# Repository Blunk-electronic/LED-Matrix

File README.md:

# LED-Matrix
A demo project to demonstrate a 2-layer PCB design

some images:

watch a short movie <http://www.blunk-electronic.de/download/dr-simon.mp4>

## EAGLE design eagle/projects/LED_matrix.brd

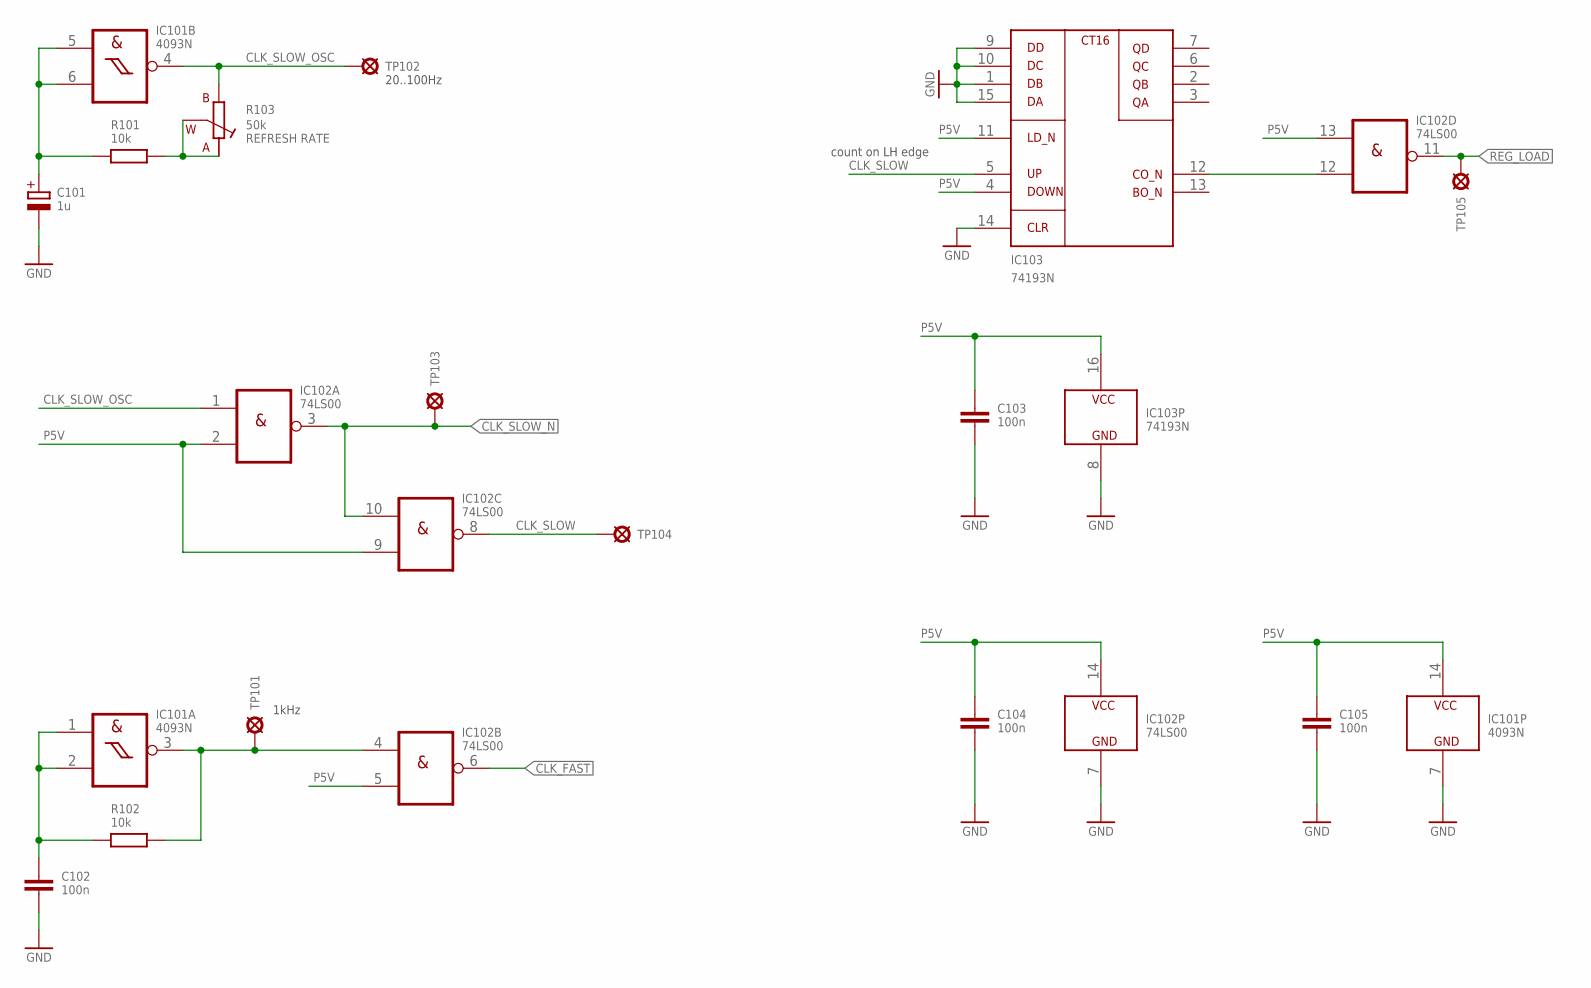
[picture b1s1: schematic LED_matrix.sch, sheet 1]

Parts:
C101: 1u; T_RADIAL_5MM_GRID_2.54MM; PART_CODE_BEL C_PAC_T_RADIAL_5mm_PITCH_2mm54_VAL_1u
C102, C103, C104, C105: 100n; T_DISC_4MM_PITCH_5MM; PART_CODE_BEL C_PAC_T_DISC_7mm_PITCH_5mm_VAL_100n
IC101: 4093N; T_NDIP14
IC102: 74LS00; T_NDIP14; PART_CODE_BEL IC_PAC_T_NDIP14_VAL_SN74LS00N
IC103: 74193N; T_NDIP16; PART_CODE_BEL IC_PAC_NDIP16_VAL_SN74193N
R101, R102: 10k; T_0207_PITCH_10MM; PART_CODE_BEL R_PAC_T_0207_PITCH_10mm_VAL_10k
R103: 50k; T_TRIM_PIHER_PT10_HORIZONTAL; PART_CODE_BEL R_PAC_T_TRIM_PIHER_PT10_HORIZONTAL_VAL_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
TP101, TP102, TP103, TP104, TP105: TEST_POINT_T_SMALL; T_TEST_POINT_SMALL

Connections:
CLK_FAST: IC102.6 (O); also elsewhere on the board
CLK_FAST_OSC: IC101.3 (O), IC102.4 (I0), R102.2, TP101.1
CLK_FAST_RC: C102.1, IC101.1 (I0), IC101.2 (I1), R102.1
CLK_SLOW: IC102.8 (O), IC103.5 (UP), TP104.1
CLK_SLOW_N: IC102.3 (O), IC102.10 (I0), TP103.1; also elsewhere on the board
CLK_SLOW_OSC: IC101.4 (O), IC102.1 (I0), R103.B, TP102.1
CLK_SLOW_RA: R101.2, R103.A, R103.W
CLK_SLOW_RC: C101.+, IC101.5 (I0), IC101.6 (I1), R101.1
CT_CO_N: IC102.12 (I1), IC103.12 (CO_N)
GND: C101.-, C102.2, C103.2, C104.2, C105.2, IC101.7 (GND), IC102.7 (GND), IC103.1 (DB), IC103.8 (GND), IC103.9 (DD), IC103.10 (DC), IC103.14 (CLR), IC103.15 (DA); also elsewhere on the board
P5V: C103.1, C104.1, C105.1, IC101.14 (VCC), IC102.2 (I1), IC102.5 (I1), IC102.9 (I1), IC102.13 (I0), IC102.14 (VCC), IC103.4 (DOWN), IC103.11 (LD_N), IC103.16 (VCC); also elsewhere on the board
REG_LOAD: IC102.11 (O), TP105.1; also elsewhere on the board

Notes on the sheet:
count on LH edge
20..100Hz
1kHz

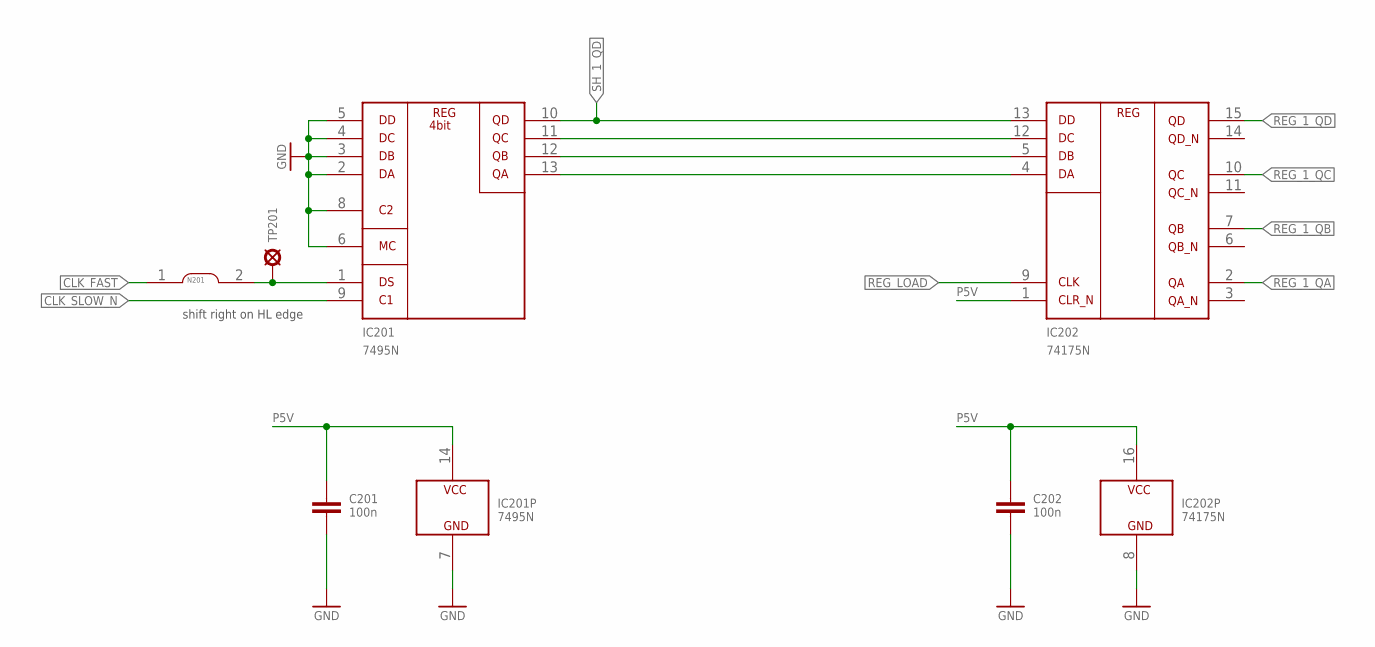
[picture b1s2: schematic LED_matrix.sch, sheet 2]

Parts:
C201, C202: 100n; T_DISC_4MM_PITCH_5MM; PART_CODE_BEL C_PAC_T_DISC_7mm_PITCH_5mm_VAL_100n
IC201: 7495N; T_NDIP14; PART_CODE_BEL IC_PAC_T_NDIP14_VAL_SN7495N
IC202: 74175N; T_NDIP16; PART_CODE_BEL IC_PAC_NDIP16_VAL_SN74175N
N201: NET_CHANGER-S-0.3MM; S_NET_CHANGER_0.3MM
TP201: TEST_POINT_T_SMALL; T_TEST_POINT_SMALL

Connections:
CLK_FAST: N201.1; also elsewhere on the board
CLK_SLOW_N: IC201.9 (C1); also elsewhere on the board
GND: C201.2, C202.2, IC201.2 (DA), IC201.3 (DB), IC201.4 (DC), IC201.5 (DD), IC201.6 (MC), IC201.7 (GND), IC201.8 (C2), IC202.8 (GND); also elsewhere on the board
P5V: C201.1, C202.1, IC201.14 (VCC), IC202.1 (CLR_N), IC202.16 (VCC); also elsewhere on the board
REG_1_QA: IC202.2 (QA); also elsewhere on the board
REG_1_QB: IC202.7 (QB); also elsewhere on the board
REG_1_QC: IC202.10 (QC); also elsewhere on the board
REG_1_QD: IC202.15 (QD); also elsewhere on the board
REG_LOAD: IC202.9 (CLK); also elsewhere on the board
SH_1_DS: IC201.1 (DS), N201.2, TP201.1
SH_1_QA: IC201.13 (QA), IC202.4 (DA)
SH_1_QB: IC201.12 (QB), IC202.5 (DB)
SH_1_QC: IC201.11 (QC), IC202.12 (DC)
SH_1_QD: IC201.10 (QD), IC202.13 (DD); also elsewhere on the board

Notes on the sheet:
shift right on HL edge

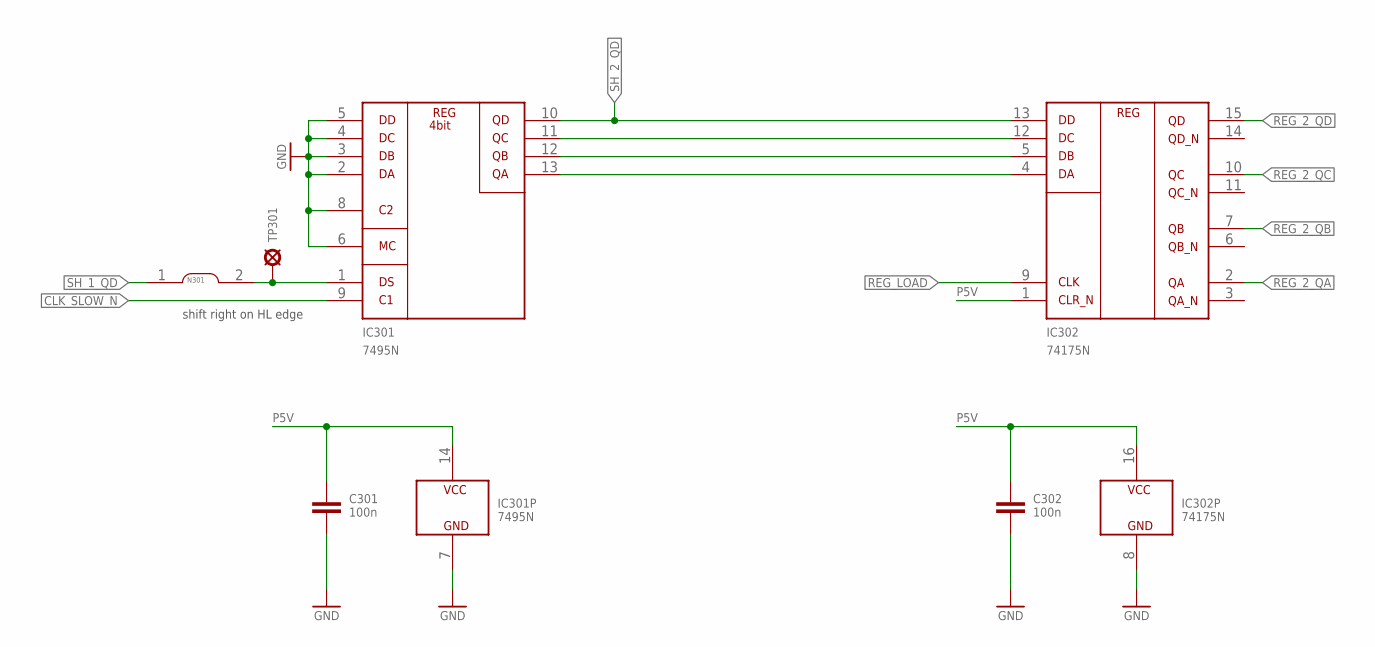
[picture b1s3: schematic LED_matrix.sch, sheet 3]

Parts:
C301, C302: 100n; T_DISC_4MM_PITCH_5MM; PART_CODE_BEL C_PAC_T_DISC_7mm_PITCH_5mm_VAL_100n
IC301: 7495N; T_NDIP14; PART_CODE_BEL IC_PAC_T_NDIP14_VAL_SN7495N
IC302: 74175N; T_NDIP16; PART_CODE_BEL IC_PAC_NDIP16_VAL_SN74175N
N301: NET_CHANGER-S-0.3MM; S_NET_CHANGER_0.3MM
TP301: TEST_POINT_T_SMALL; T_TEST_POINT_SMALL

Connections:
CLK_SLOW_N: IC301.9 (C1); also elsewhere on the board
GND: C301.2, C302.2, IC301.2 (DA), IC301.3 (DB), IC301.4 (DC), IC301.5 (DD), IC301.6 (MC), IC301.7 (GND), IC301.8 (C2), IC302.8 (GND); also elsewhere on the board
P5V: C301.1, C302.1, IC301.14 (VCC), IC302.1 (CLR_N), IC302.16 (VCC); also elsewhere on the board
REG_2_QA: IC302.2 (QA); also elsewhere on the board
REG_2_QB: IC302.7 (QB); also elsewhere on the board
REG_2_QC: IC302.10 (QC); also elsewhere on the board
REG_2_QD: IC302.15 (QD); also elsewhere on the board
REG_LOAD: IC302.9 (CLK); also elsewhere on the board
SH_1_DS1: IC301.1 (DS), N301.2, TP301.1
SH_1_QD: N301.1; also elsewhere on the board
SH_2_QA: IC301.13 (QA), IC302.4 (DA)
SH_2_QB: IC301.12 (QB), IC302.5 (DB)
SH_2_QC: IC301.11 (QC), IC302.12 (DC)
SH_2_QD: IC301.10 (QD), IC302.13 (DD); also elsewhere on the board

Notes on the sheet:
shift right on HL edge

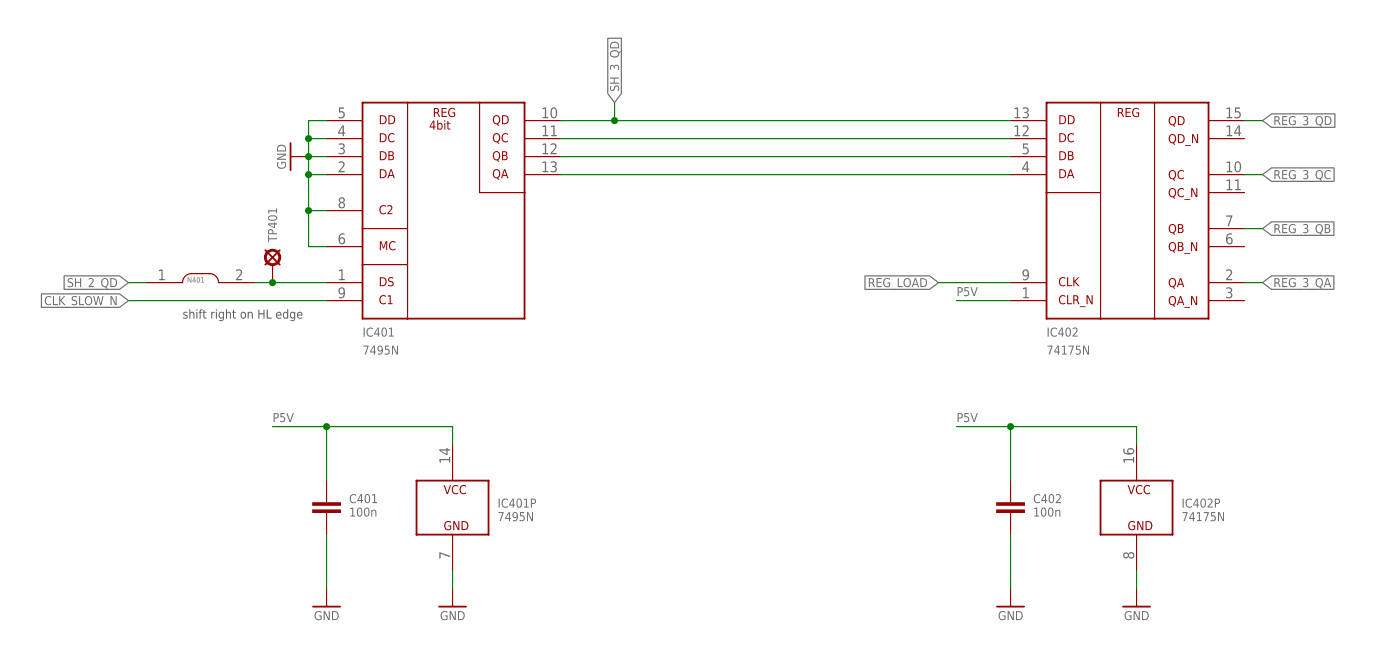
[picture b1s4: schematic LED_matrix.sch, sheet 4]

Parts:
C401, C402: 100n; T_DISC_4MM_PITCH_5MM; PART_CODE_BEL C_PAC_T_DISC_7mm_PITCH_5mm_VAL_100n
IC401: 7495N; T_NDIP14; PART_CODE_BEL IC_PAC_T_NDIP14_VAL_SN7495N
IC402: 74175N; T_NDIP16; PART_CODE_BEL IC_PAC_NDIP16_VAL_SN74175N
N401: NET_CHANGER-S-0.3MM; S_NET_CHANGER_0.3MM
TP401: TEST_POINT_T_SMALL; T_TEST_POINT_SMALL

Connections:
CLK_SLOW_N: IC401.9 (C1); also elsewhere on the board
GND: C401.2, C402.2, IC401.2 (DA), IC401.3 (DB), IC401.4 (DC), IC401.5 (DD), IC401.6 (MC), IC401.7 (GND), IC401.8 (C2), IC402.8 (GND); also elsewhere on the board
P5V: C401.1, C402.1, IC401.14 (VCC), IC402.1 (CLR_N), IC402.16 (VCC); also elsewhere on the board
REG_3_QA: IC402.2 (QA); also elsewhere on the board
REG_3_QB: IC402.7 (QB); also elsewhere on the board
REG_3_QC: IC402.10 (QC); also elsewhere on the board
REG_3_QD: IC402.15 (QD); also elsewhere on the board
REG_LOAD: IC402.9 (CLK); also elsewhere on the board
SH_1_DS2: IC401.1 (DS), N401.2, TP401.1
SH_2_QD: N401.1; also elsewhere on the board
SH_3_QA: IC401.13 (QA), IC402.4 (DA)
SH_3_QB: IC401.12 (QB), IC402.5 (DB)
SH_3_QC: IC401.11 (QC), IC402.12 (DC)
SH_3_QD: IC401.10 (QD), IC402.13 (DD); also elsewhere on the board

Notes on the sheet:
shift right on HL edge

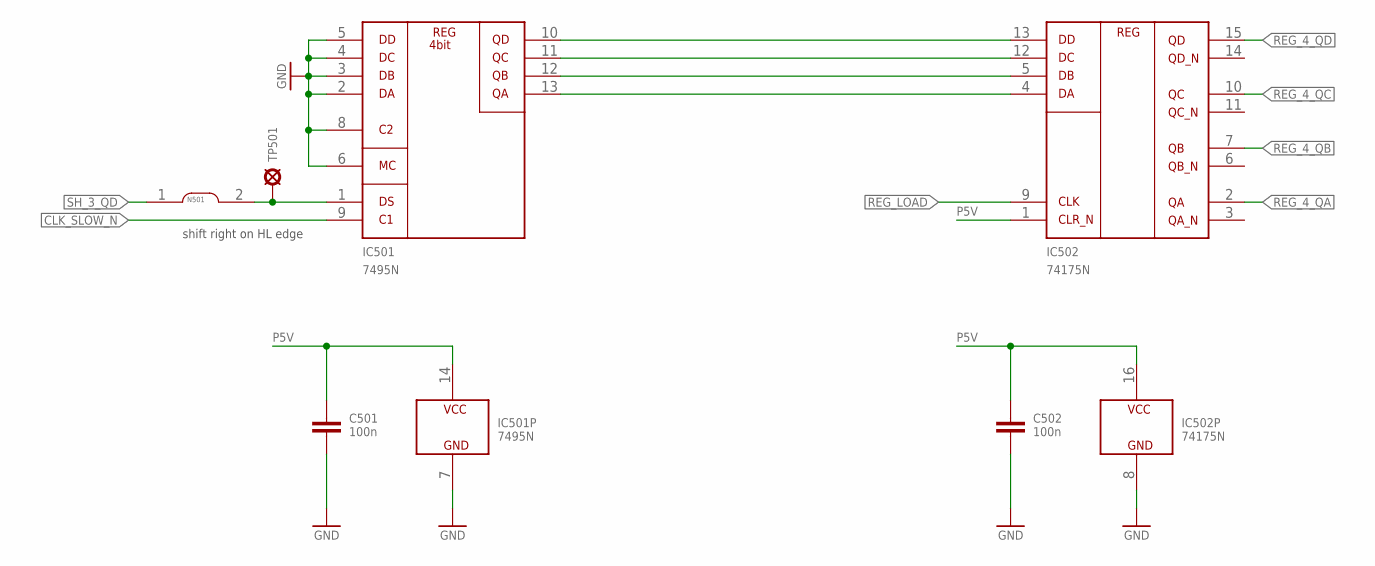
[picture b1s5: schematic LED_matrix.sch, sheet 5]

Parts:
C501, C502: 100n; T_DISC_4MM_PITCH_5MM; PART_CODE_BEL C_PAC_T_DISC_7mm_PITCH_5mm_VAL_100n
IC501: 7495N; T_NDIP14; PART_CODE_BEL IC_PAC_T_NDIP14_VAL_SN7495N
IC502: 74175N; T_NDIP16; PART_CODE_BEL IC_PAC_NDIP16_VAL_SN74175N
N501: NET_CHANGER-S-0.3MM; S_NET_CHANGER_0.3MM
TP501: TEST_POINT_T_SMALL; T_TEST_POINT_SMALL

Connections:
CLK_SLOW_N: IC501.9 (C1); also elsewhere on the board
GND: C501.2, C502.2, IC501.2 (DA), IC501.3 (DB), IC501.4 (DC), IC501.5 (DD), IC501.6 (MC), IC501.7 (GND), IC501.8 (C2), IC502.8 (GND); also elsewhere on the board
P5V: C501.1, C502.1, IC501.14 (VCC), IC502.1 (CLR_N), IC502.16 (VCC); also elsewhere on the board
REG_4_QA: IC502.2 (QA); also elsewhere on the board
REG_4_QB: IC502.7 (QB); also elsewhere on the board
REG_4_QC: IC502.10 (QC); also elsewhere on the board
REG_4_QD: IC502.15 (QD); also elsewhere on the board
REG_LOAD: IC502.9 (CLK); also elsewhere on the board
SH_1_DS3: IC501.1 (DS), N501.2, TP501.1
SH_3_QD: N501.1; also elsewhere on the board
SH_4_QA: IC501.13 (QA), IC502.4 (DA)
SH_4_QB: IC501.12 (QB), IC502.5 (DB)
SH_4_QC: IC501.11 (QC), IC502.12 (DC)
SH_4_QD: IC501.10 (QD), IC502.13 (DD)

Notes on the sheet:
shift right on HL edge

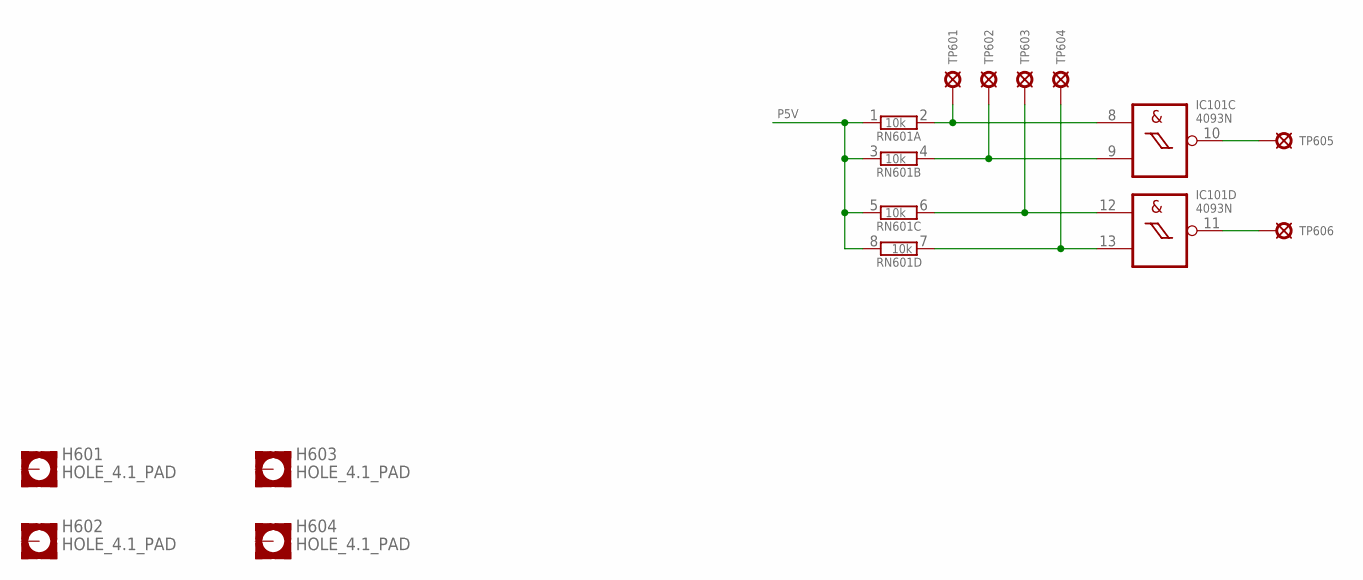
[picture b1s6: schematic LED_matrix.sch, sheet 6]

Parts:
H601, H602, H603, H604: HOLE_4.1_PAD; 4.1_PAD
IC101: 4093N; T_NDIP14
RN601: 10k; T_SIL8; PART_CODE_BEL RN_PAC_T_SIL8_VAL_10k
TP601, TP602, TP603, TP604, TP605, TP606: TEST_POINT_T_SMALL; T_TEST_POINT_SMALL

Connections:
P5V: RN601.1, RN601.3 (1), RN601.5 (1), RN601.8 (2); also elsewhere on the board
RSV_IN_1: IC101.8 (I0), RN601.2, TP601.1
RSV_IN_2: IC101.9 (I1), RN601.4 (2), TP602.1
RSV_IN_3: IC101.12 (I0), RN601.6 (2), TP603.1
RSV_IN_4: IC101.13 (I1), RN601.7 (1), TP604.1
RSV_OUT_1: IC101.10 (O), TP605.1
RSV_OUT_2: IC101.11 (O), TP606.1

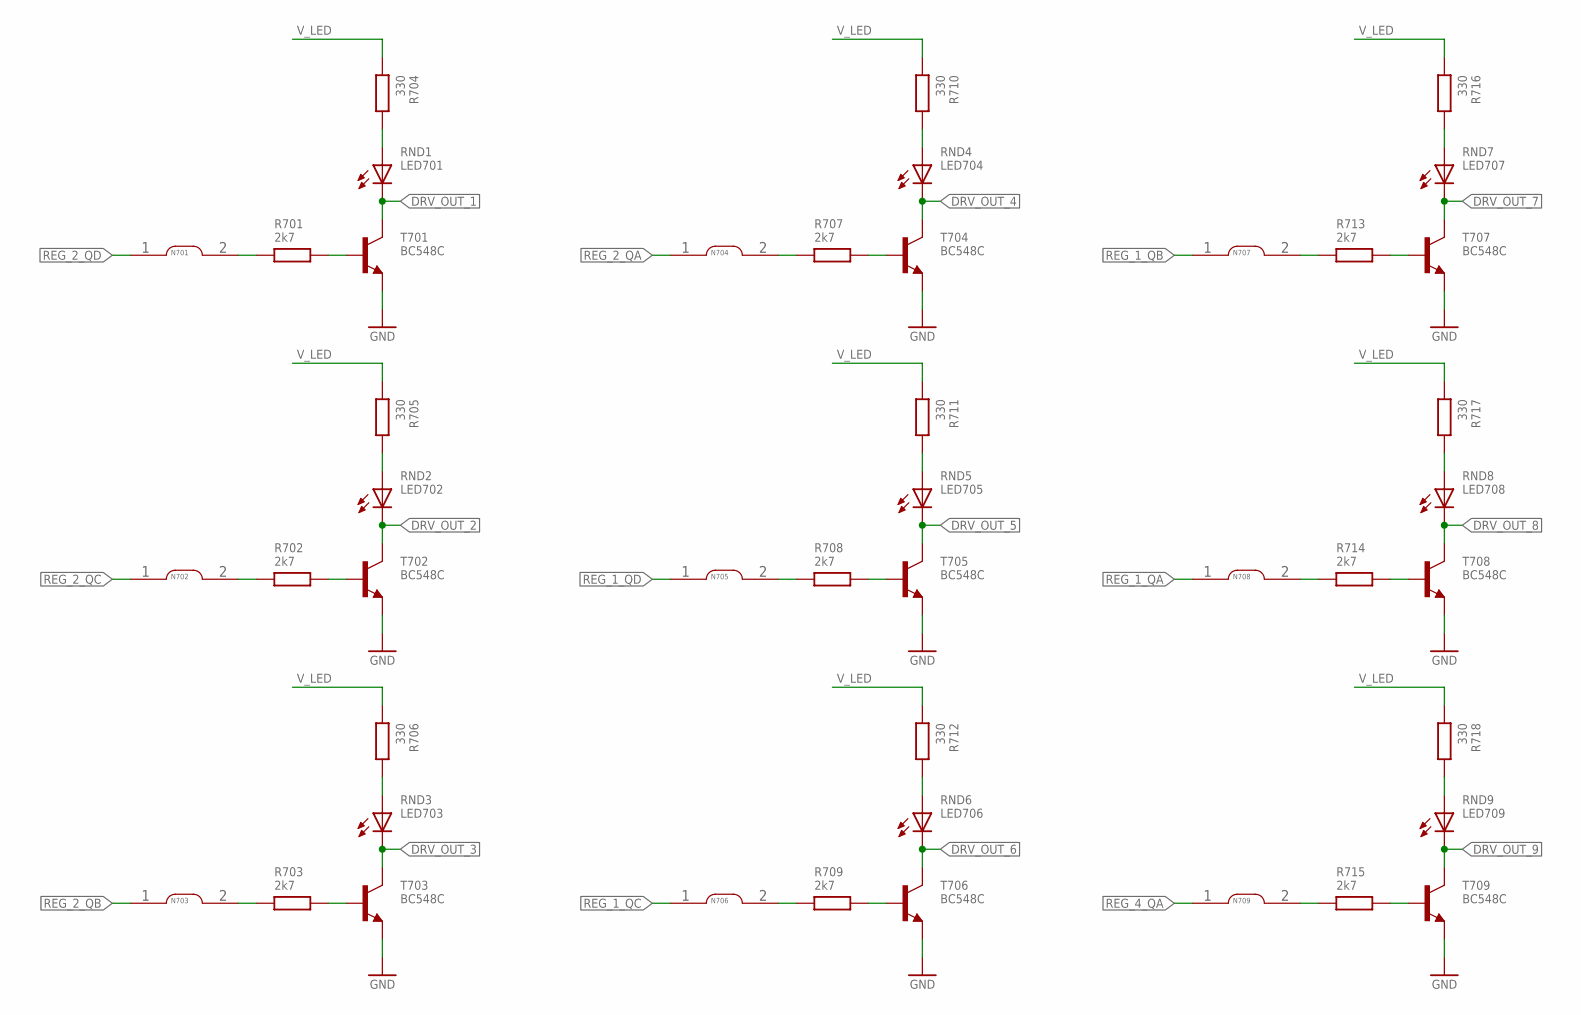
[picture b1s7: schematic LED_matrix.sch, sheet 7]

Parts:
LED701, LED702, LED703, LED704, LED705, LED706, LED707, LED708, LED709: LED_T_ROUND_3MM; T_ROUND_3MM
N701, N702, N703, N704, N705, N706, N707, N708, N709: NET_CHANGER-S-0.3MM; S_NET_CHANGER_0.3MM
R701, R702, R703, R707, R708, R709, R713, R714, R715: 2k7; T_0207_PITCH_10MM
R704, R705, R706, R710, R711, R712, R716, R717, R718: 330; T_0207_PITCH_10MM; PART_CODE_BEL R_PAC_T_0207_PITCH_10mm_VAL_330
T701, T702, T703, T704, T705, T706, T707, T708, T709: BC548C; T_TO92-CBE

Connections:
DRV_IN_1: N701.2, R701.1
DRV_IN_2: N702.2, R702.1
DRV_IN_3: N703.2, R703.1
DRV_IN_4: N704.2, R707.1
DRV_IN_5: N705.2, R708.1
DRV_IN_6: N706.2, R709.1
DRV_IN_7: N707.2, R713.1
DRV_IN_8: N708.2, R714.1
DRV_IN_9: N709.2, R715.1
DRV_IN_B1: R701.2, T701.B
DRV_IN_B2: R702.2, T702.B
DRV_IN_B3: R703.2, T703.B
DRV_IN_B4: R707.2, T704.B
DRV_IN_B5: R708.2, T705.B
DRV_IN_B6: R709.2, T706.B
DRV_IN_B7: R713.2, T707.B
DRV_IN_B8: R714.2, T708.B
DRV_IN_B9: R715.2, T709.B
DRV_OUT_1: LED701.C, T701.C; also elsewhere on the board
DRV_OUT_2: LED702.C, T702.C; also elsewhere on the board
DRV_OUT_3: LED703.C, T703.C; also elsewhere on the board
DRV_OUT_4: LED704.C, T704.C; also elsewhere on the board
DRV_OUT_5: LED705.C, T705.C; also elsewhere on the board
DRV_OUT_6: LED706.C, T706.C; also elsewhere on the board
DRV_OUT_7: LED707.C, T707.C; also elsewhere on the board
DRV_OUT_8: LED708.C, T708.C; also elsewhere on the board
DRV_OUT_9: LED709.C, T709.C; also elsewhere on the board
DRV_OUT_A_1: LED701.A, R704.2
DRV_OUT_A_2: LED702.A, R705.2
DRV_OUT_A_3: LED703.A, R706.2
DRV_OUT_A_4: LED704.A, R710.2
DRV_OUT_A_5: LED705.A, R711.2
DRV_OUT_A_6: LED706.A, R712.2
DRV_OUT_A_7: LED707.A, R716.2
DRV_OUT_A_8: LED708.A, R717.2
DRV_OUT_A_9: LED709.A, R718.2
GND: T701.E, T702.E, T703.E, T704.E, T705.E, T706.E, T707.E, T708.E, T709.E; also elsewhere on the board
REG_1_QA: N708.1; also elsewhere on the board
REG_1_QB: N707.1; also elsewhere on the board
REG_1_QC: N706.1; also elsewhere on the board
REG_1_QD: N705.1; also elsewhere on the board
REG_2_QA: N704.1; also elsewhere on the board
REG_2_QB: N703.1; also elsewhere on the board
REG_2_QC: N702.1; also elsewhere on the board
REG_2_QD: N701.1; also elsewhere on the board
REG_4_QA: N709.1; also elsewhere on the board
V_LED: R704.1, R705.1, R706.1, R710.1, R711.1, R712.1, R716.1, R717.1, R718.1; also elsewhere on the board

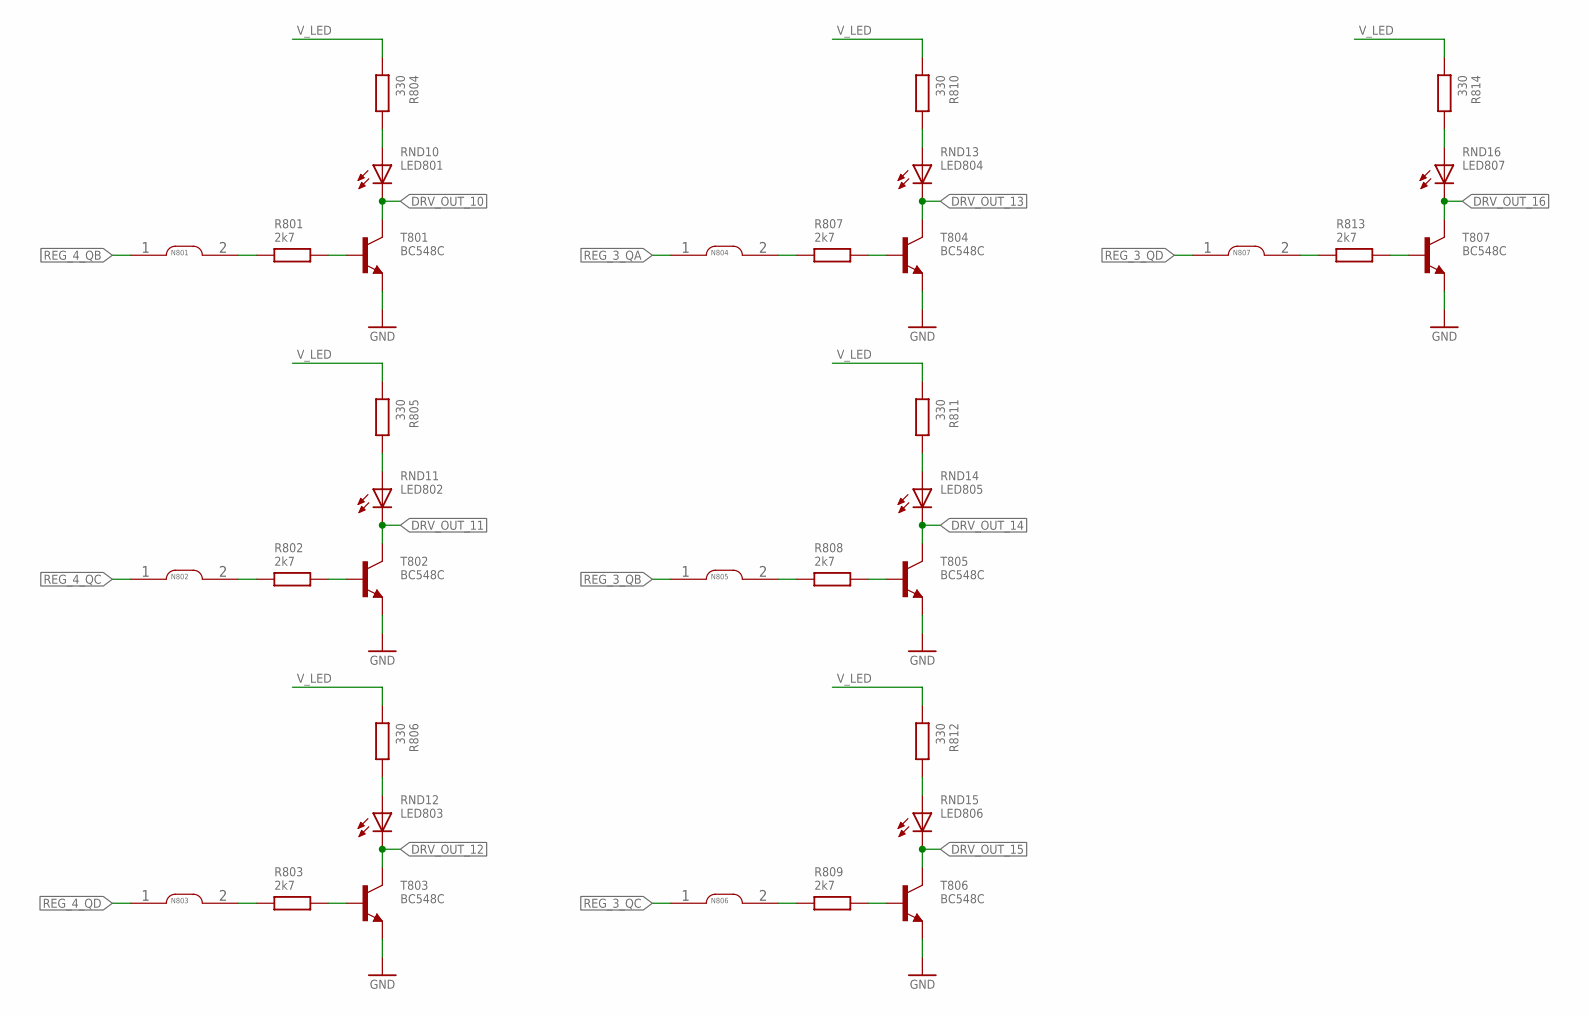
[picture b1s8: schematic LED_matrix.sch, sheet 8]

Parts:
LED801, LED802, LED803, LED804, LED805, LED806, LED807: LED_T_ROUND_3MM; T_ROUND_3MM
N801, N802, N803, N804, N805, N806, N807: NET_CHANGER-S-0.3MM; S_NET_CHANGER_0.3MM
R801, R802, R803, R807, R808, R809, R813: 2k7; T_0207_PITCH_10MM
R804, R805, R806, R810, R811, R812, R814: 330; T_0207_PITCH_10MM; PART_CODE_BEL R_PAC_T_0207_PITCH_10mm_VAL_330
T801, T802, T803, T804, T805, T806, T807: BC548C; T_TO92-CBE

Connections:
DRV_IN_10: N801.2, R801.1
DRV_IN_11: N802.2, R802.1
DRV_IN_12: N803.2, R803.1
DRV_IN_13: N804.2, R807.1
DRV_IN_14: N805.2, R808.1
DRV_IN_15: N806.2, R809.1
DRV_IN_16: N807.2, R813.1
DRV_IN_B10: R801.2, T801.B
DRV_IN_B11: R802.2, T802.B
DRV_IN_B12: R803.2, T803.B
DRV_IN_B13: R807.2, T804.B
DRV_IN_B14: R808.2, T805.B
DRV_IN_B15: R809.2, T806.B
DRV_IN_B16: R813.2, T807.B
DRV_OUT_10: LED801.C, T801.C; also elsewhere on the board
DRV_OUT_11: LED802.C, T802.C; also elsewhere on the board
DRV_OUT_12: LED803.C, T803.C; also elsewhere on the board
DRV_OUT_13: LED804.C, T804.C; also elsewhere on the board
DRV_OUT_14: LED805.C, T805.C; also elsewhere on the board
DRV_OUT_15: LED806.C, T806.C; also elsewhere on the board
DRV_OUT_16: LED807.C, T807.C; also elsewhere on the board
DRV_OUT_A_10: LED801.A, R804.2
DRV_OUT_A_11: LED802.A, R805.2
DRV_OUT_A_12: LED803.A, R806.2
DRV_OUT_A_13: LED804.A, R810.2
DRV_OUT_A_14: LED805.A, R811.2
DRV_OUT_A_15: LED806.A, R812.2
DRV_OUT_A_16: LED807.A, R814.2
GND: T801.E, T802.E, T803.E, T804.E, T805.E, T806.E, T807.E; also elsewhere on the board
REG_3_QA: N804.1; also elsewhere on the board
REG_3_QB: N805.1; also elsewhere on the board
REG_3_QC: N806.1; also elsewhere on the board
REG_3_QD: N807.1; also elsewhere on the board
REG_4_QB: N801.1; also elsewhere on the board
REG_4_QC: N802.1; also elsewhere on the board
REG_4_QD: N803.1; also elsewhere on the board
V_LED: R804.1, R805.1, R806.1, R810.1, R811.1, R812.1, R814.1; also elsewhere on the board

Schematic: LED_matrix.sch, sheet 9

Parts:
C901: 100n; T_DISC_4MM_PITCH_5MM; PART_CODE_BEL C_PAC_S_0805_VAL_100n
C902: 47n; T_DISC_4MM_PITCH_5MM; PART_CODE_BEL C_PAC_S_0805_VAL_47n
C903: 10n; T_DISC_4MM_PITCH_5MM; PART_CODE_BEL C_PAC_S_0805_VAL_10n
D901: SAY32; T_MINIPLAST
IC901: NE555V; T_NDIP8; PART_CODE_BEL IC_PAC_T_NDIP8_VAL_NE555V
R901: 1k2; T_0207_PITCH_10MM; PART_CODE_BEL R_PAC_S_0805_VAL_10k
R902: not fitted; T_0207_PITCH_10MM; PART_CODE_BEL R_PAC_S_0805_VAL_470k
R903: 1k; T_0207_PITCH_10MM; PART_CODE_BEL R_PAC_S_0805_VAL_1k
R904: 1M; T_TRIM_PIHER_PT10_HORIZONTAL
R905: 10k; T_0207_PITCH_10MM; PART_CODE_BEL R_PAC_S_0805_VAL_10k
R906: 330; T_0207_PITCH_10MM; PART_CODE_BEL R_PAC_S_0805_VAL_330
RPH901: RPH; T_TO39-2
T901: BD136; T_TO126_VERTICAL

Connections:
GND: C901.2, C902.2, C903.2, IC901.1 (GND); also elsewhere on the board
P5V: C901.1, IC901.8 (VCC), R902.2, R903.2, R905.2, T901.E; also elsewhere on the board
TIM_1: C903.1, IC901.4 (RST#), IC901.5 (OC)
TIM_2: C902.1, D901.C, IC901.2 (TRG), IC901.6 (TRSHLD), R901.1
TIM_3: D901.A, IC901.7 (DSCHRG), R901.2, R902.1, R904.B, RPH901.2
TIM_OUT: IC901.3 (OUT), R905.1, R906.1
TIM_OUT_B: R906.2, T901.B
TIM_RA: R903.1, R904.A, R904.W, RPH901.1
V_LED: T901.C; also elsewhere on the board

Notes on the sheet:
dark: 200Hz bright: 10kHz 50us fixed low time

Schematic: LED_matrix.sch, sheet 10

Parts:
C1001: 470u; T_RADIAL_16MM_GRID_7.5MM
C1002: 330n; T_DISC_7MM_PITCH_5MM
C1003: 100n; T_DISC_4MM_PITCH_5MM
D1001, D1002, D1003, D1004: 1N4001; T_DO201_GRID_18MM
IC1001: 7805_T_HORIZONTAL; T_TO220-3_HORIZONTAL
J1001: SOLDER_JUMPER-N; S_SOLDER_JUMPER_NARROW
LED1001: green; T_ROUND_3MM; PART_CODE_BEL LED_PAC_T_ROUND_3mm_VAL_green
R1001: 330; T_0207_PITCH_10MM; PART_CODE_BEL R_PAC_T_0207_PITCH_10mm_VAL_330
X1001: CLAMP_1X2-T-5MM; T_WIRE_CLAMP_1X2_PITCH_5MM

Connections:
GND: C1001.-, C1002.2, C1003.2, D1003.A, D1004.A, IC1001.2 (GND), LED1001.C; also elsewhere on the board
P5V: C1003.1, IC1001.3 (OUT), J1001.1; also elsewhere on the board
PWR_IN_AC1: D1001.A, D1003.C, X1001.2
PWR_IN_AC2: D1002.A, D1004.C, X1001.1
PWR_IN_VREG: C1001.+, C1002.1, D1001.C, D1002.C, IC1001.1 (IN)
PWR_LED: LED1001.A, R1001.2
PWR_LED_JP: J1001.2, R1001.1

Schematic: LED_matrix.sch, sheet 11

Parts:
X1101: MALE_2X13-T-VERTICAL_PITCH_2MM54; T_MALE_2X13_VERTICAL_PITCH_2MM54

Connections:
DRV_OUT_1: X1101.1; also elsewhere on the board
DRV_OUT_2: X1101.3; also elsewhere on the board
DRV_OUT_3: X1101.5; also elsewhere on the board
DRV_OUT_4: X1101.7; also elsewhere on the board
DRV_OUT_5: X1101.9; also elsewhere on the board
DRV_OUT_6: X1101.11; also elsewhere on the board
DRV_OUT_7: X1101.13; also elsewhere on the board
DRV_OUT_8: X1101.15; also elsewhere on the board
DRV_OUT_9: X1101.17; also elsewhere on the board
DRV_OUT_10: X1101.19; also elsewhere on the board
DRV_OUT_11: X1101.21; also elsewhere on the board
DRV_OUT_12: X1101.23; also elsewhere on the board
DRV_OUT_13: X1101.25; also elsewhere on the board
DRV_OUT_14: X1101.2; also elsewhere on the board
DRV_OUT_15: X1101.4; also elsewhere on the board
DRV_OUT_16: X1101.6; also elsewhere on the board
GND: X1101.8, X1101.10, X1101.12, X1101.14, X1101.16, X1101.18; also elsewhere on the board
P5V: X1101.20, X1101.22, X1101.24, X1101.26; also elsewhere on the board

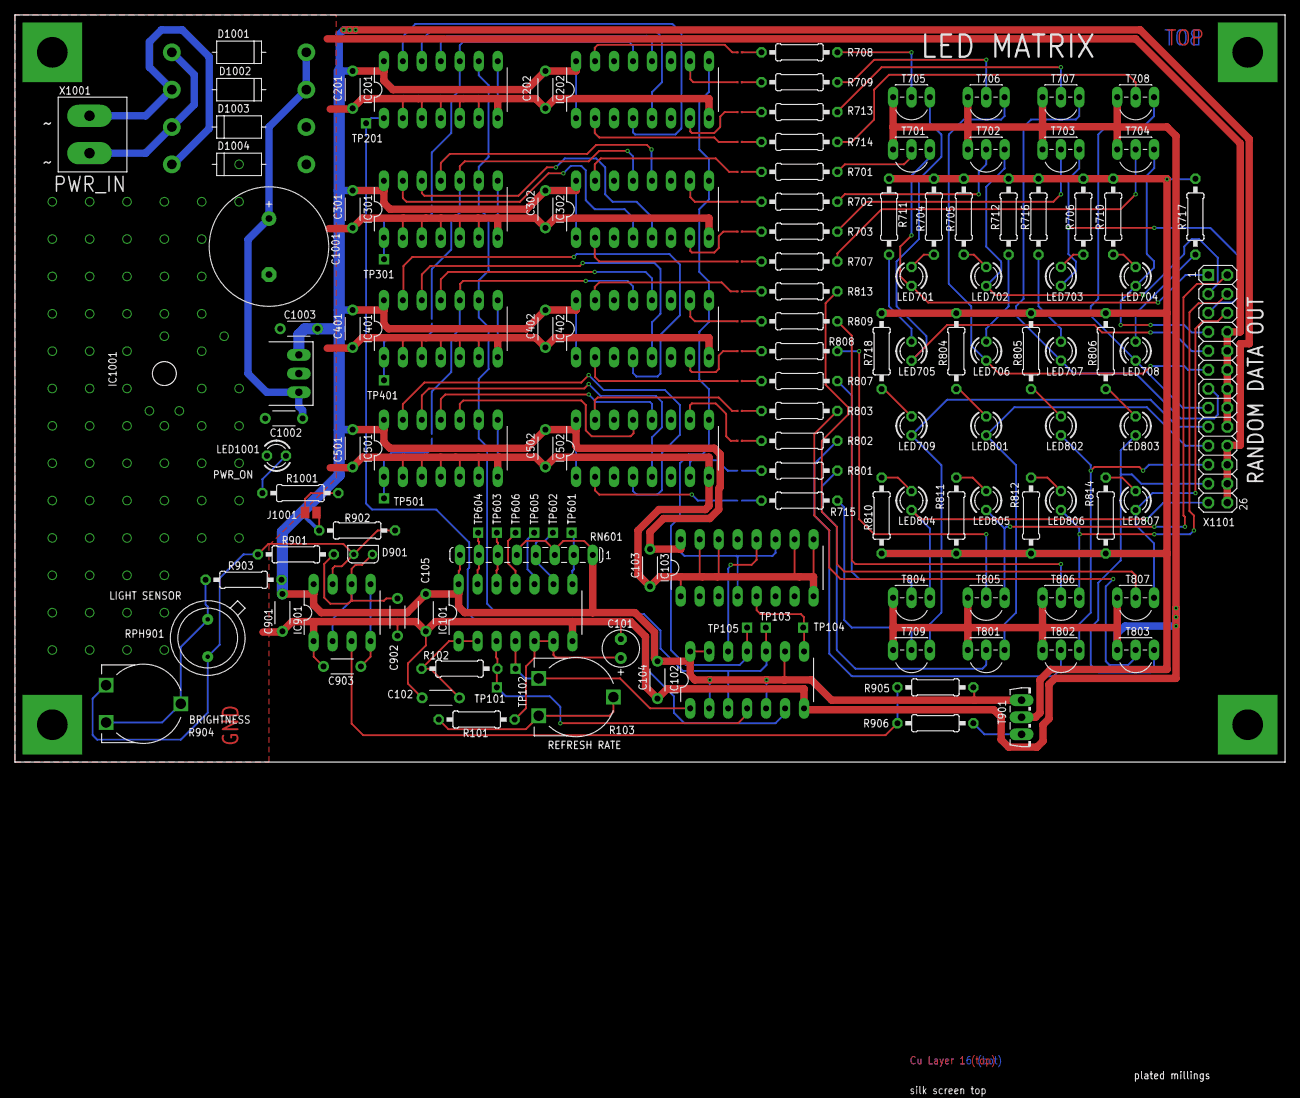
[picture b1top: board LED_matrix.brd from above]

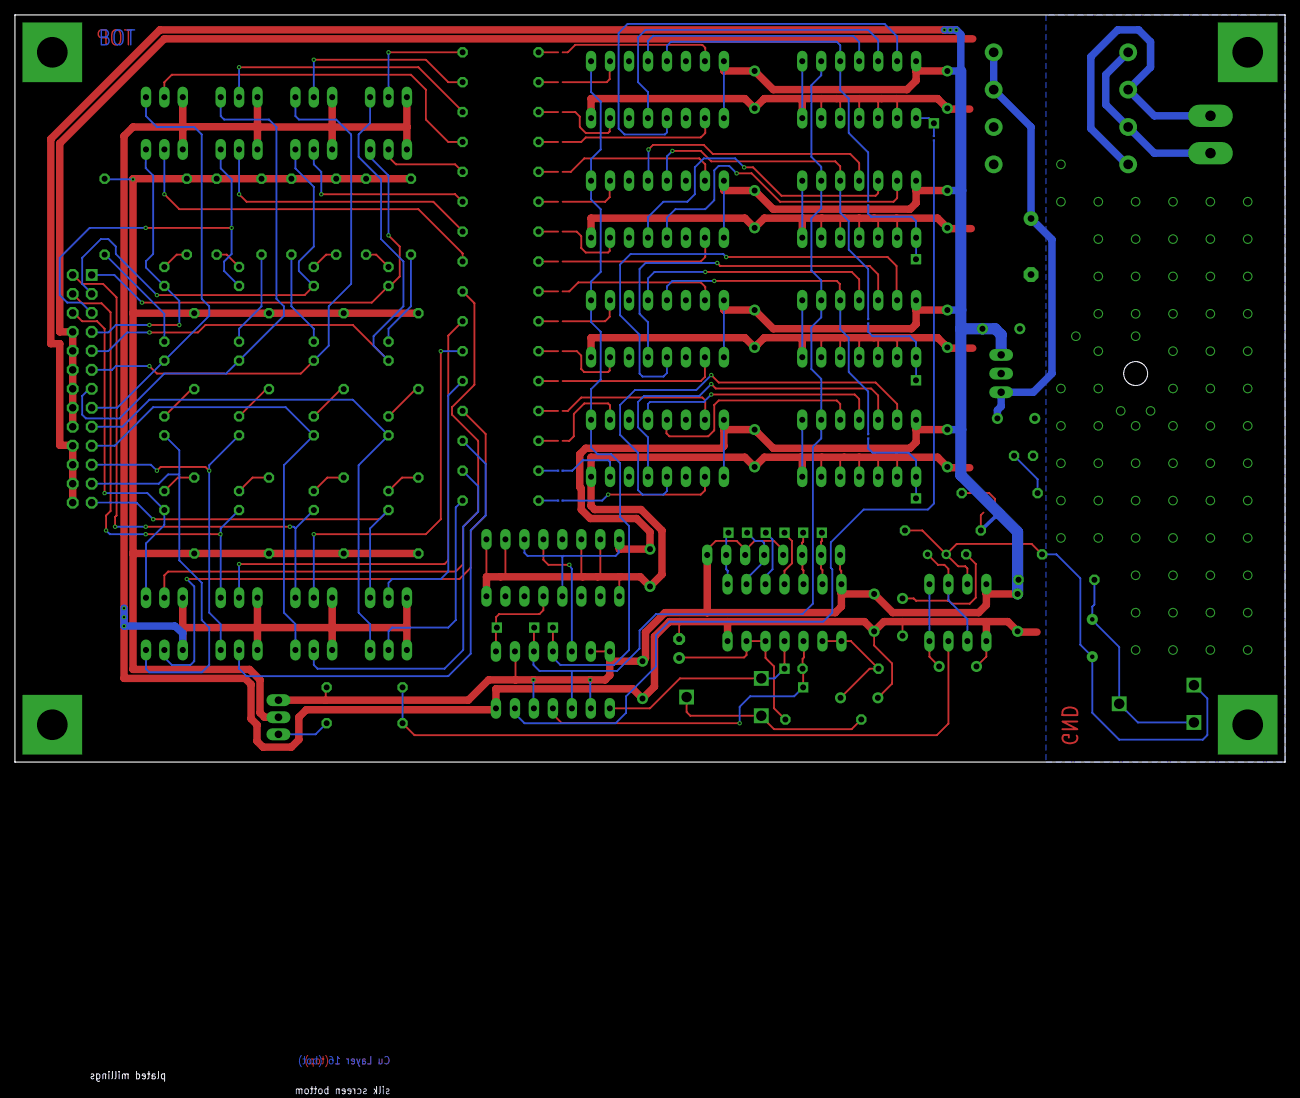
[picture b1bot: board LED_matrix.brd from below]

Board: 2 copper layers, 170.0 x 143.0 mm, 158 parts (6 on the bottom side), 130 nets.

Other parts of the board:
U$1: A4_LANDSCAPE

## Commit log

2019-01-30 sch and brd file
2019-01-31 perpare for release
2019-03-16 changed values for oscillators
2019-08-11 change default path for scripts
2019-08-11 add LED resistors
2019-08-19 route vled
2019-08-27 change scriipt dir
2019-10-08 rename anonymous nets
2019-10-08 release
2019-12-19 fix values. add movie
2019-12-19 add img

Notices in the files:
parts and their libraries:
be_frame: Copyright(C) Blunk electronic
